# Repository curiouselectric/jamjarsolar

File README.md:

# jamjarsolar
A simple DIY kit to make a solar powered light from an old jam jar. Design files and instructions.

This kit is available from The Curious Electric Company here:
https://www.curiouselectric.co.uk/

This is a simple DIY soldering and construction kit.

This repository includes the following:

* PCB design files and schematic. Produced using KiCAD.
* Hardware for the kit.
* Instructions for the kit.

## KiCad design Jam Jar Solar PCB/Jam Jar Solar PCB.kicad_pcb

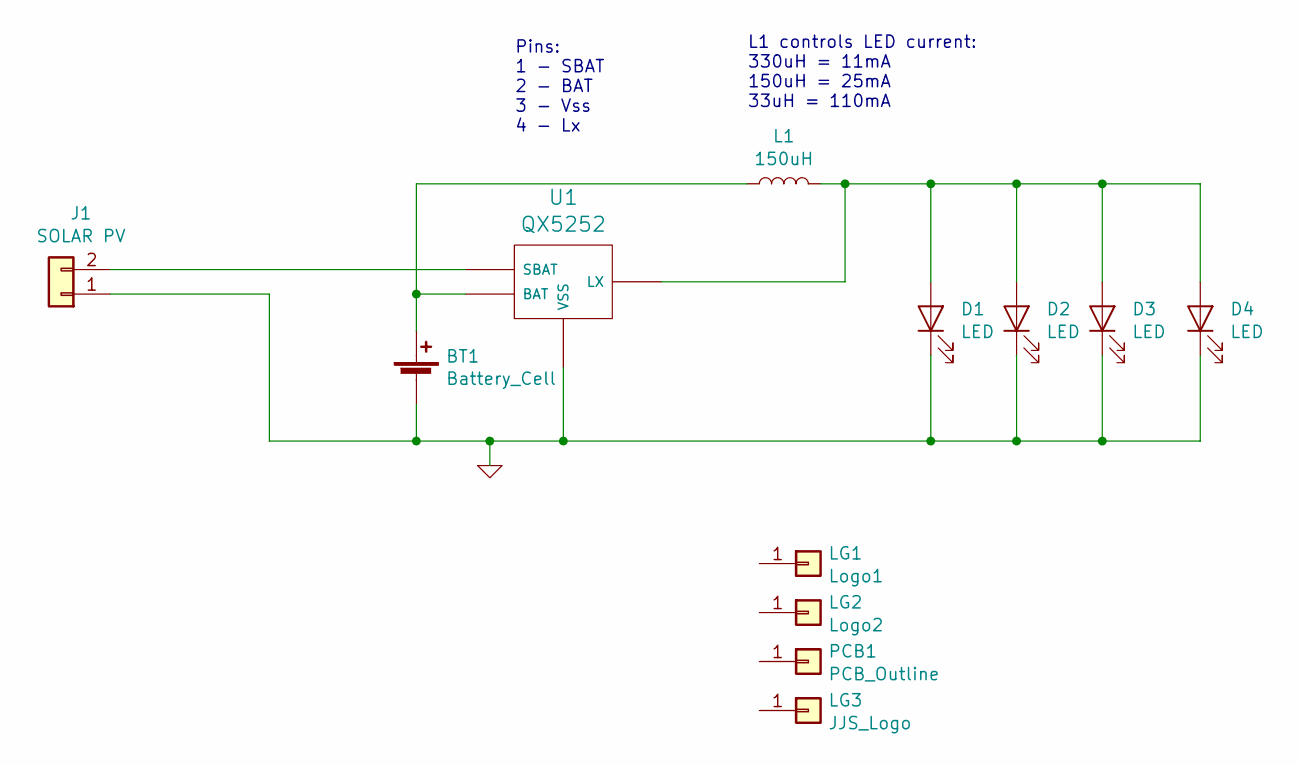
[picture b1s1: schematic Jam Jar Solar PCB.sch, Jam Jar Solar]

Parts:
BT1: Battery_Cell; Batt_Holder_AAA
D1, D2, D3, D4: LED; TH_LED-5MM_larg_pad
J1: SOLAR PV; Solar_PV_TH_SMD
L1: 150uH; TH_Inductor_JJS
LG1: Logo1; TCEC_Words_13mm
LG2: Logo2; 2020_04_14_CuriousElectricCompany_Logo_Round_15mm_FCu
LG3: JJS_Logo; JJS_Jar_logo
PCB1: PCB_Outline; JJS_PCB_Outline
U1: QX5252; TH_QX5252

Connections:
GND: BT1.2 (-), D1.1 (K), D2.1 (K), D3.1 (K), D4.1 (K), J1.1, U1.3 (VSS)
unnamed: BT1.1 (+), L1.1, U1.2 (BAT)
unnamed: D1.2 (A), D2.2 (A), D3.2 (A), D4.2 (A), L1.2, U1.4 (LX)
unnamed: J1.2, U1.1 (SBAT)

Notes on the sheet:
L1 controls LED current: 330uH = 11mA 150uH = 25mA 33uH = 110mA
Pins: 1 - SBAT 2 - BAT 3 - Vss 4 - Lx

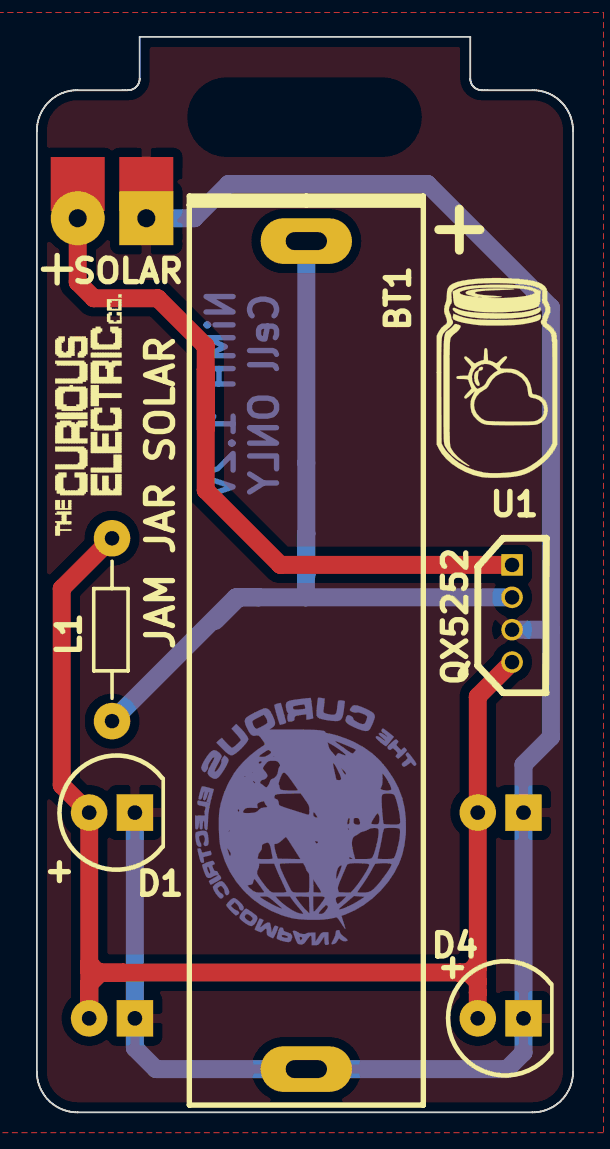
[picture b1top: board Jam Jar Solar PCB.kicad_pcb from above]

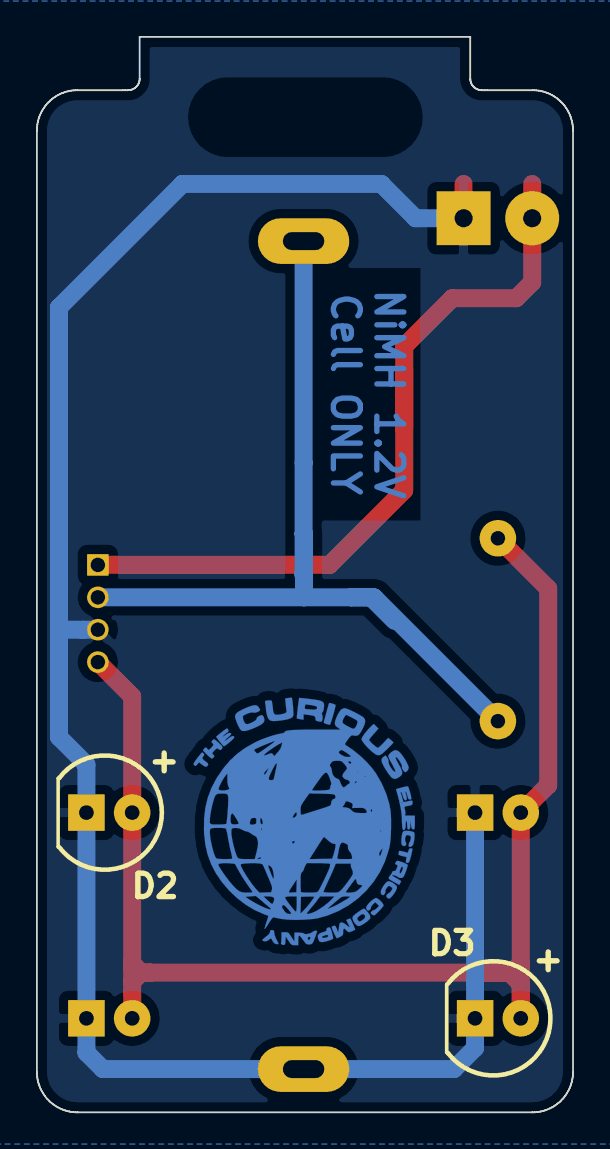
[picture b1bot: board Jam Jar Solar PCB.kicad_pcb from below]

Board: 2 copper layers, 29.8 x 59.7 mm, 12 parts (3 on the bottom side), 4 nets.

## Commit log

2020-11-29 Initial commit of PCB files
2020-12-05 Updated Instructions and Hardware
2020-12-11 Update of PCB and Instructions
